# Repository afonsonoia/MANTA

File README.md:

# MANTA – Embedded AI & Vision-Guided Autonomous Flight Platform

**MANTA** is an experimental fixed-wing UAV research platform designed for investigating embedded computer vision, attitude stabilization, and autonomous navigation in GPS-denied environments.

Rather than relying on commercial black-box autopilots, MANTA is engineered from the ground up as an open, modular avionics architecture: combining low-level deterministic real-time control (ESP32) with high-level onboard perception and video recording (Raspberry Pi 3 A+ companion computer).

> **Origin of the Name**: *MANTA* is a regional term from Madeira Island, Portugal, designating the local population of the Common Buzzard (*Buteo buteo rothschildi*), a resident bird of prey known for soaring effortlessly across the island's steep oceanic mountains.

---

## In-Flight Validation & Onboard Camera Footage

MANTA has achieved fully stabilized flight under closed-loop fly-by-wire control with calibrated attitude PIDs, verified aerodynamic handling, and active onboard video recording.

The companion computer (**Raspberry Pi 3 A+**) flies onboard with a dedicated camera module, executing an autonomous power-loss-immune recording pipeline (`.mkv`) with sport shutter tuning to eliminate motor vibration artifacts and rolling shutter jello.

### Onboard Flight Video

<p align="center">
  
  <br>
  <em>▶️ <b>Watch the flight video</b> — Aerial footage captured directly by the onboard Raspberry Pi 3 A+ camera during flight tests. <b><a href="https://www.youtube.com/watch?v=h6kUTQn7zuM&t=90s" target="_blank">Click here or on the image above to play on YouTube starting at 1:30 min</a></b>.</em>
</p>

### Pre-Flight Preparation & Avionics Checkout

<p align="center">
  
  <br>
  <em>Pre-flight checkout at the flight field: LiPo battery installation, 6-axis IMU zeroing, radio link verification, and autonomous companion computer boot sequence before launch.</em>
</p>

During field operations, pre-flight checks verify the full avionics chain:
1. **Airframe & Propulsion**: 4S LiPo battery securement, Hobbywing Skywalker 40A V2 ESC throttle arming, and control horn linkage checks.
2. **IMU & Attitude Zeroing**: Static 6-axis MPU6050 accelerometer and gyroscope calibration with mounting offsets (+9.2° Pitch, +4.4° Roll).
3. **Control Surface Trims**: V-tail ruddervator and elevon zero-point verification across all 4 servos within calibrated hardware limits.
4. **LoRa Telemetry Handshake**: 20 Hz binary telemetry downlink reception and acoustic buzzer confirmation on the Ground Station ESP32.
5. **Companion Boot**: Autonomous transition of the Raspberry Pi 3 A+ into Field Mode with RF blocking and continuous video capture.

---

## Avionics & Embedded Hardware Architecture

MANTA uses a custom-manufactured dual-board shield architecture designed in KiCad, cleanly distributing high-current motor power and low-noise sensor signals while fitting into the airframe fuselage.

<p align="center">
  
  <br>
  <em>Complete assembled avionics stack: Custom dual-board PCB shield, ESP32 flight controller, LoRa 433 MHz RF link, Air530 GPS antenna, dual LM2596S switching buck converters, precision voltage divider, and Hobbywing Skywalker 40A V2-UBEC ESC.</em>
</p>

### Core Hardware Components

| Subsystem | Component | Role / Specification |
|---|---|---|
| **Flight Controller** | ESP32-WROOM-32 (240 MHz Dual-Core) | Real-time 100 Hz attitude estimation, RC receiver pulse decoding, PI-D control loops, V-tail servo mixing, and 20 Hz LoRa telemetry. |
| **Companion Computer** | Raspberry Pi 3 A+ (64-bit Quad-Core) | Camera management, high-bitrate in-flight video recording, visual place recognition (VPR), and future autonomous vision navigation. |
| **In-Flight Camera** | Sony IMX378-79 Sensor Module | High-resolution aerial video capture, 2x2 binned low-latency readout, and visual feature extraction. |
| **Inertial Measurement (IMU)** | MPU6050 (6-Axis Accel / Gyro) | High-rate attitude determination running Mahony AHRS quaternion fusion filter at 100 Hz. |
| **Barometric Altimeter** | BMP280 | Static pressure sensing, relative barometric altitude tracking, and vertical velocity estimation over I2C. |
| **RF Telemetry Link** | SX1278 LoRa Transceiver (433 MHz) | Long-range 20 Hz binary telemetry downlink (SF7, BW 250 kHz, CR 4/5, CRC16) streaming flight dynamics to the ground. |
| **Satellite Navigation** | Air530 Multi-GNSS Module | Global positioning reference, ground track velocity, and satellite constellation tracking over hardware UART. |
| **Electronic Speed Control (ESC)** | Hobbywing Skywalker 40A V2-UBEC | 3S–4S LiPo motor speed control with integrated 5V/5A switching BEC powering the avionics bus. |
| **Power Regulation** | Dual LM2596S DC-DC Regulators | Independent 5.1V / 3A power rails dedicated to the Raspberry Pi companion computer and servo bus, isolating control logic from servo voltage sag. |
| **Battery Monitoring** | Precision Calibrated Voltage Divider | Calibrated ADC sensing validated to within 0.062V of multimeter ground truth across 3S/4S voltage curves. |

### Custom Manufactured PCB Shields

<p align="center">

  <br>
  <em>KiCad Dual-Board Shield Layouts: Power Distribution Board & Data / Sensor Board</em>
</p>

- **Two-Board Architecture**: Separates noisy high-current traces (motor ESC, LiPo leads, buck regulators) on the Power Board from sensitive analog sensors (MPU6050, BMP280, LoRa SPI bus, RC receiver lines) on the Data Board.
- **Continuous Ground Pours**: Low-impedance ground returns and copper shielding prevent motor/ESC switching noise from coupling into the RF frontend or ADC measurements.

### Pinout & GPIO Mapping

```
RC Receiver Inputs:                  Servo & ESC Outputs:
  CH1 (Roll / Rollerons): Pin D39      Back Right (BR / V-Tail): Pin D13
  CH2 (Pitch / Elevator): Pin D34      Back Left  (BL / V-Tail): Pin D14
  CH3 (Throttle / ESC):   Pin D35      Front Right (FR / Flap):  Pin D27
  CH4 (Aux / Rudder):     Pin D32      Front Left  (FL / Flap):  Pin D26
  CH5 (Mode SWC + SWB):   Pin D33      Motor Throttle / ESC:     Pin D25

Buses & Peripherals:
  LoRa SX1278 (VSPI):     SCK=18, MISO=19, MOSI=23, CS=5, DIO0=4
  I2C Sensors (IMU+BMP):  SDA=21, SCL=22
  Air530 GNSS (UART2):    RX2=16, TX2=17
  Battery Voltage ADC:    Pin D36 (VP)
```

---

## Flight Control Architecture & Calibrated PIDs

MANTA utilizes a hybrid V-tail mixing scheme where Pitch is controlled by the rear ruddervators (BR/BL) and Roll is controlled by the front control surfaces (FR/FL), with elevator assist.

```mermaid
flowchart TD
    subgraph Inputs [Pilot & Sensor Inputs]
        RC[RC Receiver CH1-CH5]
        IMU[MPU6050 6-Axis IMU]
        BARO[BMP280 Barometer]
    end

    subgraph StateEst [Attitude Estimation]
        IMU --> Mahony[100 Hz Mahony AHRS Filter]
        Mahony --> Att[Pitch & Roll Euler Angles]
    end

    subgraph ControlCore [Flight Control Core]
        RC --> ModeSelect{Flight Mode Selector\nCH5 SWC + SWB}
        Att --> ModeSelect

        ModeSelect -->|Mode 1| M1[Manual Pitch + Roll Assist]
        ModeSelect -->|Mode 2| M2[FBW Pitch PI-D + FBW Roll PI-D]
        ModeSelect -->|Mode 3| M3[FBW Pitch PI-D + Adaptive Extremum Seeking Roll]

        SWB{Flaperons SWB} -->|Active| Flaps[20° Down Flaperon Governor]
    end

    subgraph Mixing [Actuator Mixer & Anti-Saturation]
        M1 & M2 & M3 --> Mixer[V-Tail & Wing Mixer]
        Flaps --> Mixer
        Mixer --> Headroom[Headroom Scaling & Anti-Saturation]
    end

    subgraph Outputs [Physical Actuators]
        Headroom --> Servos[BR / BL / FR / FL Servos + ESC]
    end
```

### Flight Modes (Transmitter CH5: SWC + SWB)

The pilot switches flight modes in real time via transmitter switches **SWC** (3-position mode switch) and **SWB** (2-position flaperon switch):

| SWC | SWB | CH5 PWM | Active Mode | Flaperons | Control Characteristics |
|:---:|:---:|:---:|:---:|:---:|:---|
| 1 | OFF | **1166 µs** | **Mode 1** | **OFF** | **Manual Pitch + Roll Assist**: Direct pilot pitch authority with active IMU bank angle attenuation and automatic wing leveling. |
| 2 | OFF | **1328 µs** | **Mode 2** | **OFF** | **FBW PI-D Auto-Level**: Closed-loop Pitch PI-D auto-leveling and Roll PI-D stabilization. |
| 3 | OFF | **1411 µs** | **Mode 3** | **OFF** | **FBW Adaptive**: Pitch PI-D leveling + Extremum Seeking adaptive roll PID tuning. |
| 1 | ON  | **1541 µs** | **Mode 1** | **ON**  | Manual Pitch + Roll Assist with **+20.0° DOWN Flaperons**. |
| 2 | ON  | **1825 µs** | **Mode 2** | **ON**  | FBW Pitch PI-D + Roll PI-D with **+20.0° DOWN Flaperons**. |
| 3 | ON  | **1942 µs** | **Mode 2** *(Auto)* | **ON**  | **Automatic Safety Demotion to Mode 2** + Flaperons (prevents adaptive gain corruption during approach). |

### Control Features & Safety Mechanisms

1. **Permanent Roll Assist (Mode 1)**:
   - Full ±20° pilot authority near wings level (0° roll).
   - Progressive linear bank angle attenuation up to 60°:
     $$\text{Max Roll Command} = 20^\circ \times \left(1 - \frac{|\text{Roll}|}{60^\circ}\right)$$
   - Active auto-recovery: If roll exceeds 60°, an automatic 5° opposite leveling bias is injected while retaining full pilot recovery command.
2. **Pitch PI-D Closed-Loop Control**:
   - Strictly negative feedback equation: $\text{pitchDiff} = -\text{constrain}(\text{pitchPidOut})$.
   - Anti-stall climb limit clamped to 25° ($K_p = 5.00$).
   - Anti-windup integrator ceiling limited to $\pm 100\,\mu\text{s}$ ($\pm 9.0^\circ$ of trim authority), guaranteeing 64% dynamic headroom for proportional and derivative action.
3. **Flaperons Approach Governor & Anti-Saturation**:
   - Deploys up to **+20.0° DOWN** ($\pm 222\,\mu\text{s}$) on front control surfaces (FR/FL) to dramatically increase lift coefficient ($C_L$) and drag ($C_D$) for slow, stable landings.
   - Smooth linear throttle governor between $1200\,\mu\text{s}$ (full deflection) and $1500\,\mu\text{s}$ (fully retracted).
   - **Headroom Scaling**: Pilot roll command maintains 100% priority. When roll commands approach mechanical limits, flaperon deflection is automatically scaled down (`flaperonHeadroom = 1.0 - |rollDiff| / anglePulseLimit`), preventing servo binding and maintaining roll control without clipping.

### Static Surface Calibration & Trims

All control surfaces operate strictly within the hardware safety span $[1000, 2000]\,\mu\text{s}$ centered around calibrated mechanical neutral points:

| Surface | Pin | Neutral PWM | Static Trim | Angular Span | Description |
|---|:---:|:---:|:---:|:---:|---|
| **BR (Back Right)** | D13 | **1478 µs** | $-2.0^\circ$ ($-22\,\mu\text{s}$) | $1200 - 1756\,\mu\text{s}$ | $+2.0^\circ$ UP nose-up compensation for level glide in manual mode. |
| **BL (Back Left)**  | D14 | **1633 µs** | $-12.0^\circ$ ($+133\,\mu\text{s}$) | $1355 - 1911\,\mu\text{s}$ | $+2.0^\circ$ UP inverted V-tail compensation. |
| **FR (Front Right)**| D27 | **1500 µs** | $0.0^\circ$ ($0\,\mu\text{s}$) | $1222 - 1778\,\mu\text{s}$ | True mechanical center. |
| **FL (Front Left)** | D26 | **1544 µs** | $+4.0^\circ$ ($+44\,\mu\text{s}$) | $1266 - 1822\,\mu\text{s}$ | Horn spline offset alignment defining flat wing zero. |

- **IMU Pitch Mounting Offset**: $+9.2^\circ$ (longitudinal leveling reference).
- **IMU Roll Mounting Offset**: $+4.4^\circ$ ($+1.9^\circ$ airframe bias $+ 2.5^\circ$ left-roll compensation for straight flight).

---

## Companion Computer & Video Pipeline (Raspberry Pi 3 A+)

The Raspberry Pi 3 A+ companion computer provides onboard vision processing and in-flight video capture:

```mermaid
flowchart LR
    Power[Power On Pi] --> BootService[manta-boot.service]
    BootService --> Check{Wi-Fi detected\n< 30 seconds?}

    Check -->|YES| DevMode[Bench / Dev Mode]
    DevMode --> GitPull[git pull]
    DevMode --> SSH[SSH & Wi-Fi Active]
    DevMode --> CamIdle[Camera Free for CV]

    Check -->|NO| FlightMode[Field / Flight Mode]
    FlightMode --> RFKill[rfkill: Block 2.4 GHz RF]
    FlightMode --> HDMIOff[Disable HDMI Circuitry]
    FlightMode --> AutoRec[Continuous .mkv Safe Recording]
```

### Autonomous Dual-Mode Boot Stack (`manta_boot.sh`)
- **Bench / Dev Mode (Wi-Fi Detected < 30s)**: Pi keeps Wi-Fi and SSH active, syncs codebase, and leaves the camera open for interactive computer vision development.
- **Field / Flight Mode (No Wi-Fi < 30s)**:
  - **RF Cutoff**: Disables Wi-Fi and Bluetooth (`rfkill block all`) to eliminate 2.4 GHz interference with the RC receiver and LoRa link while conserving battery power.
  - **HDMI Power-Down**: Shuts down the HDMI display subsystem (`vcgencmd display_power 0`), saving ~30 mA.
  - **Autonomous Safe Recording**: Launches `record_flight.sh` saving video directly to local storage.
- **Anti-Lockout Mechanism**: Multi-layer startup unblocking (`ExecStartPre=+`, NetworkManager re-activation, and interface scan) guarantees the Pi can reconnect to Wi-Fi whenever returning to the workshop.

### Power-Loss Immunity & Video Optimizations
- **Matroska (`.mkv`) Container**: Traditional MP4 files corrupt if power drops before the file header is finalized. MANTA records in Matroska with synchronous cluster flushing (`--flush`), ensuring video remains 100% playable right up to the exact moment the LiPo is disconnected upon landing.
- **Anti-Jello & Sport Shutter**: Uses 2x2 sensor pixel binning (halving sensor readout time), fast sport shutter exposure, manual focus locked to infinity, and temporal denoiser disabled to prevent motion blur and rolling shutter vibration skew.

---

## Ground Station & Telemetry Architecture

<p align="center">
  
  <br>
  <em>Dedicated Ground Station hardware: ESP32 receiver, 433 MHz LoRa module, and piezo acoustic warning buzzer streaming live telemetry over USB to the PC Mission Planner.</em>
</p>

### Simplex Downlink Protocol
- **Aircraft Transmitter (Simplex TX)**: Transmits 20 Hz binary telemetry packets (61 bytes nominal / up to 74 bytes with GNSS and failsafe data) protected by CRC16. The aircraft has no LoRa receiver listening overhead, ensuring uninterrupted flight control loop execution.
- **Ground Station Receiver (Simplex RX)**: Receives LoRa packets and streams them over USB Serial (`115200 baud`) to the PC Ground Station application while driving an onboard piezo buzzer.
- **Acoustic Warning System**: Emits audible alerts for link loss, critical battery states, and distinct 700 ms confirmation beeps upon flight mode transitions (SWC/SWB).

### Ground Station Software Suite

| Tool | Path | Description |
|---|---|---|
| **Mission Planner** | [`Code/GROUND-STATION/MANTA_MISSION_PLANNER.py`](file:///c:/Users/Afonso%20Noia/PycharmProjects/BlueSky/Code/GROUND-STATION/MANTA_MISSION_PLANNER.py) | Full-featured PC HUD displaying artificial horizon, compass, altitude, battery gauge, RSSI/SNR signal metrics, GPS map tracking, and flight mode state. |
| **Flight Replay Simulator** | [`Code/GROUND-STATION/replay_flight_mission_planner.py`](file:///c:/Users/Afonso%20Noia/PycharmProjects/BlueSky/Code/GROUND-STATION/replay_flight_mission_planner.py) | Replays recorded flight logs (`flight_logs/manta_flight_XXXX.csv`) through the Mission Planner HUD for post-flight analysis. |
| **FPV Explorer** | [`Code/Computer Vision/manta_explorer.py`](file:///c:/Users/Afonso%20Noia/PycharmProjects/BlueSky/Code/Computer Vision/manta_explorer.py) | Desktop GUI for previewing, browsing, and inspecting in-flight camera videos captured by the Raspberry Pi. |
| **Video Retrieval** | [`Code/Computer Vision/download_videos.py`](file:///c:/Users/Afonso%20Noia/PycharmProjects/BlueSky/Code/Computer Vision/download_videos.py) | Automated tool for pulling flight recordings from the Raspberry Pi over SCP/SFTP. |
| **PID SysID Tuner** | [`Code/GROUND-STATION/tune_pid_sysid.py`](file:///c:/Users/Afonso%20Noia/PycharmProjects/BlueSky/Code/GROUND-STATION/tune_pid_sysid.py) | System identification and PID tuning tool using recorded flight telemetry. |

---

## Repository Structure

```
├── .agents/                        # Aircraft configuration, pin mapping & control rules
├── Code/
│   ├── Battery_Monitor/            # Battery voltage calibration and ESC logger GUI
│   ├── Computer Vision/
│   │   ├── demos/                  # Visual Place Recognition (VPR) MobileNet + KNN experiments
│   │   ├── Simulator/              # Python flight dynamics simulator & PID visualization
│   │   ├── convert_videos.py       # H.264 / MKV video converter & re-muxer
│   │   ├── download_videos.py      # Automated flight video downloader from Raspberry Pi
│   │   └── manta_explorer.py       # Desktop FPV video explorer and review GUI
│   ├── GROUND-STATION/
│   │   ├── include/ & src/         # ESP32 Ground Station receiver firmware (PlatformIO)
│   │   ├── MANTA_MISSION_PLANNER.py # PC HUD Ground Station & telemetry dashboard
│   │   ├── replay_flight_mission_planner.py # Post-flight telemetry replay tool
│   │   ├── telemetry_codec.py      # Python binary telemetry packet encoder/decoder
│   │   ├── telemetry_csv_logger.py # Asynchronous high-rate flight log recorder
│   │   └── tune_pid_sysid.py       # Telemetry-based PID tuning and SysID analyzer
│   ├── MANTA_ESP32/
│   │   ├── include/ & src/         # Main flight controller C++ firmware (PlatformIO)
│   │   │   ├── control.cpp         # 100 Hz PI-D, Roll Assist, Flaperons governor & mixer
│   │   │   ├── mpu6050.cpp         # Mahony AHRS quaternion attitude estimation
│   │   │   ├── receiver.cpp        # 5-channel RC pulse decoder & deadband filtering
│   │   │   ├── network.cpp         # 20 Hz binary LoRa telemetry transmission
│   │   │   ├── bmp280.cpp          # I2C barometric altitude & pressure tracking
│   │   │   └── gps.cpp             # Hardware UART GNSS parsing & auto-pin detection
│   │   └── platformio.ini          # ESP32 build configuration & dependencies
│   └── MANTA_PI/
│       ├── manta_boot.sh           # Autonomous dual-mode boot manager (Bench vs Flight)
│       ├── manta-boot.service      # Systemd boot service for Raspberry Pi
│       ├── record_flight.sh        # Power-loss safe in-flight video recording
│       └── stream_flight.sh        # Low-latency live video streaming script
├── Electronics/
│   ├── DATA/                       # KiCad PCB layout & schematic (Data / Sensor Board)
│   └── POWER/                      # KiCad PCB layout & schematic (Power Distribution Board)
├── media/
│   └── general_images/             # Flight banner, in-flight video thumbnail, hardware photos & PCB layouts
├── tests/                          # 171 automated CI/CD unit & integration tests
└── run_tests.py                    # Master CI/CD test runner
```

---

## CI/CD Test Suite & Verification

The codebase includes an extensive automated test suite covering firmware compilation, control kinematics, telemetry codecs, fail-safes, and analytical sensor accuracy:

```bash
python run_tests.py
```

```
============================================================================
                  MANTA AVIONICS CI/CD TEST SUITE RUNNER            
============================================================================
  SUCCESS: All 171 MANTA CI/CD tests PASSED cleanly! (53.82s)
  Categories Verified:
    [PASS] Firmware & Python Compilation (PlatformIO ESP32 & Ground Station)
    [PASS] Fly-By-Wire Control, PI-D & Kinematics
    [PASS] Simplex Telemetry Codec & Protocols (Fuzzing, Bit-Corruption Rejection)
    [PASS] Flight Safety, Failsafes & SysID Alignment
    [PASS] Sensor Calibration & Ground Truth Verification (Voltage error < 0.062V)
============================================================================
```

---

## Project Roadmap

### Phase 1: Hardware Proof-of-Concepts (POC)
- [x] Establish ESP32 communications with peripheral sensors (BMP280, LoRa, Voltage sensor).
- [x] Implement RC receiver pulse width reading and telemetry logs.
- [x] Establish initial LoRa communication between aircraft and ground station.
- [x] Set up lightweight visual place recognition experiments using aerial imagery databases.
- [x] Perform isolated bench tests for each sensor to ensure accuracy and data reliability.

### Phase 2: Airframe Assembly & Avionics Integration
- [x] Assemble the main airframe skeleton and mount propulsion/control surfaces.
- [x] Complete custom KiCad PCB schematics and dual-board layout routing.
- [x] Manufacture physical dual-board PCB shield architecture (Power & Data boards).
- [x] Validate power distribution, dual BEC outputs, and sensor bus continuity.
- [x] Experimentally calibrate battery voltage conversion against multimeter ground truth (< 0.062V error).
- [x] Mount core avionics and electronics on the airframe.
- [x] Conduct EMI testing ensuring motor/ESC switching noise does not disrupt GPS or LoRa RF link.
- [x] Deploy robust LoRa telemetry (20 Hz binary codec, non-blocking Ground Station logging).
- [x] Execute maiden field flights in manual mode to validate airframe aerodynamics and ground station link.

### Phase 3: Flight Control & Fly-By-Wire Stabilization
- [x] Integrate 6-axis MPU6050 Mahony AHRS quaternion sensor fusion (100 Hz) into ESP32 firmware.
- [x] Implement attitude-aware roll envelope protection and progressive bank angle limiting on RC Channel 5.
- [x] Implement and calibrate closed-loop PI-D controllers for Pitch (rear V-tail) and Roll (front surfaces).
- [x] Implement 20° flaperons approach governor with dynamic headroom anti-saturation scaling.
- [x] Conduct field flight tests to calibrate PIDs for smooth, wind-resistant fly-by-wire leveling.
- [x] Mount and integrate Raspberry Pi 3 A+ companion computer and onboard camera module.
- [x] Deploy autonomous dual-mode boot stack and power-loss-immune flight video recording (`.mkv`).
- [x] Validate closed-loop flight stability and record in-flight aerial footage.

### Phase 4: Autonomous Waypoint Navigation & Path-Planning
- [ ] Implement interactive trajectory planner in PC Ground Station UI to select waypoints on a map.
- [ ] Transmit pre-planned path coordinates from Mission Planner to aircraft over wireless link.
- [ ] Develop onboard navigation controller fusing GPS, BMP280 barometric altitude, and IMU data.
- [ ] Validate autonomous waypoint-to-waypoint navigation, altitude hold, heading lock, and fail-safe Return-to-Home (RTH).
- [ ] Execute autonomous field flight missions to verify trajectory accuracy and fail-safe reliability.

### Phase 5: Onboard Vision & Visual Place Recognition (VPR)
- [x] Design custom mount and install Raspberry Pi 3 A+ companion computer and camera module on airframe.
- [x] Execute onboard high-rate video logging and autonomous flight capture.
- [ ] Set up ESP32-to-Raspberry Pi high-speed serial communication protocol (UART / telemetry bridge).
- [ ] Deploy lightweight Visual Place Recognition (VPR) for image-based GPS-denied position estimation.
- [ ] Develop computer vision pipelines for visual horizon detection and landmark/mountain recognition.
- [ ] Test real-time visual perception and localization during autonomous flight.
- [ ] Perform comprehensive flight campaigns evaluating vision-based localization precision under real operational conditions.

---

## Authors & Acknowledgments

- **Afonso Nóia** — Aircraft design, custom PCB hardware, firmware development, fly-by-wire control algorithms, companion computer software, and flight testing.
- Platform development and field testing conducted on Madeira Island, Portugal.

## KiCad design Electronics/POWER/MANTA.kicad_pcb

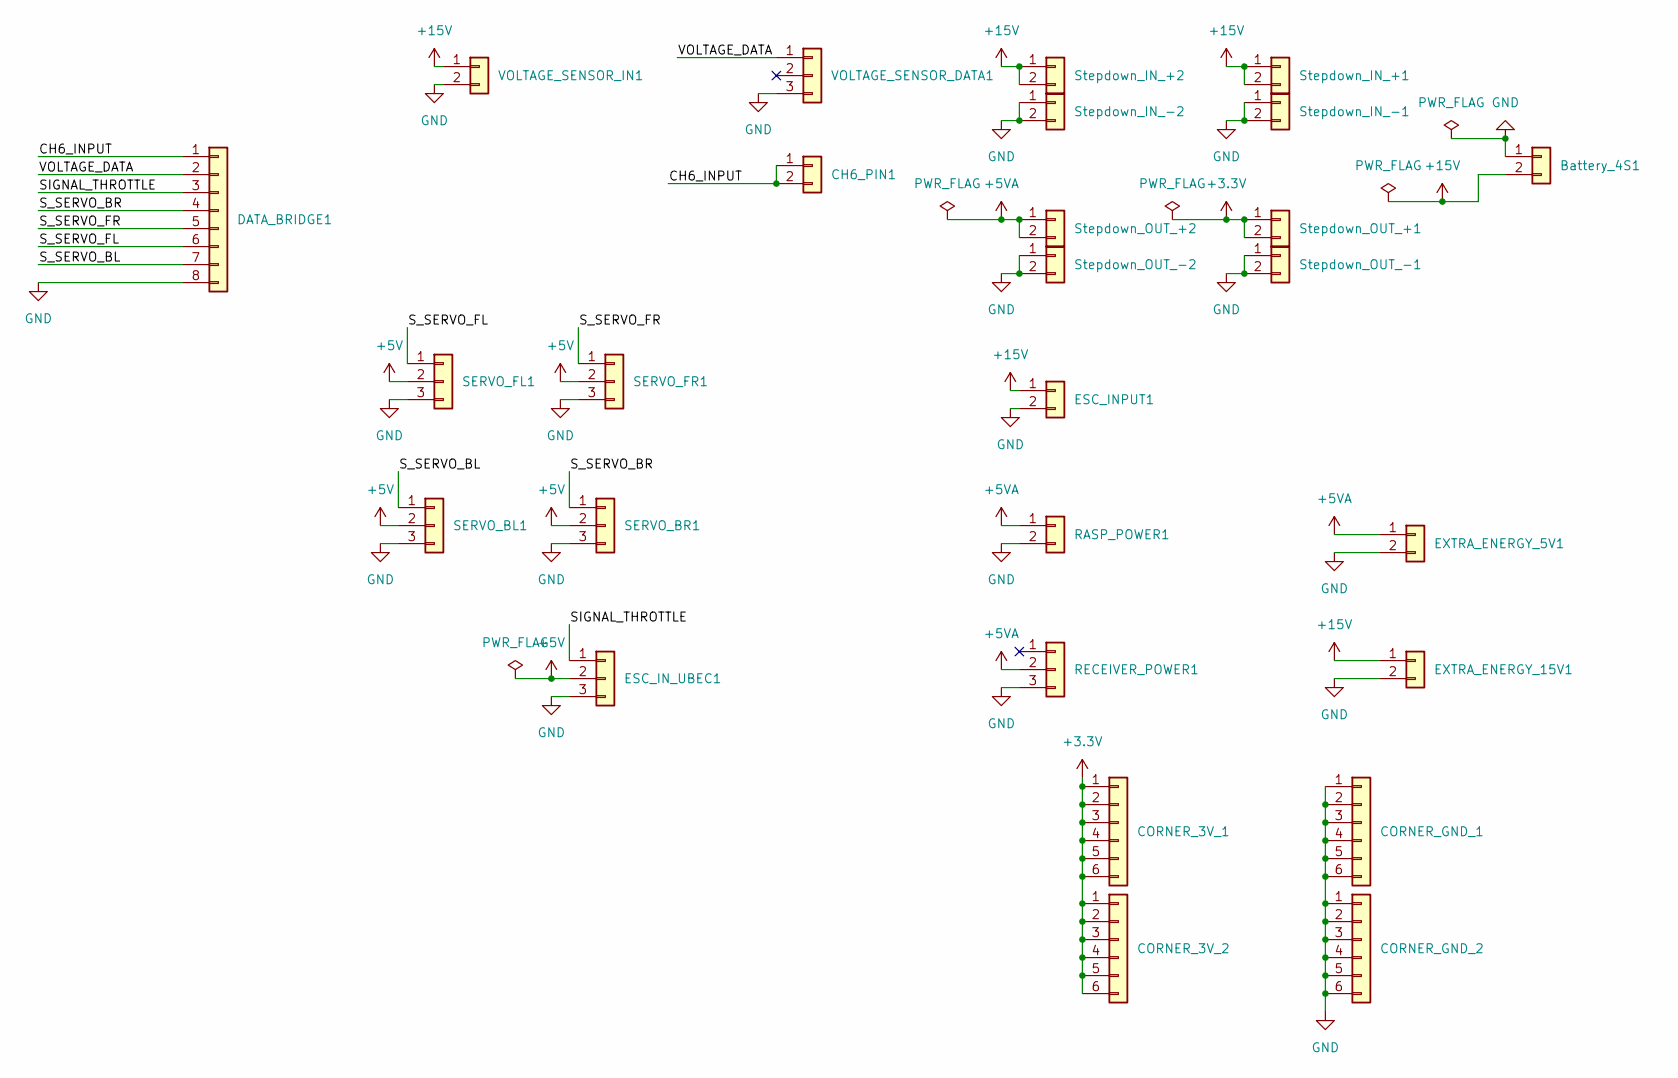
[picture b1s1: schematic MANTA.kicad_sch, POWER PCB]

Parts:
Battery_4S1: Conn_01x02; AMASS_XT60PW-M_1x02_P7.20mm_Horizontal
CH6_PIN1: Conn_01x02; PinHeader_1x02_P2.54mm_Vertical
CORNER_3V_1, CORNER_3V_2: Conn_01x06; PinHeader_1x06_P2.54mm_Vertical
CORNER_GND_1, CORNER_GND_2: Conn_01x06; PinHeader_1x06_P2.54mm_Vertical
DATA_BRIDGE1: Conn_01x08; PinHeader_1x08_P2.54mm_Vertical
ESC_INPUT1: SolderWire-2.5sqmm_1x02_P8.8mm_D2.4mm_OD4.4mm
ESC_IN_UBEC1: Conn_01x03; PinHeader_1x03_P2.54mm_Vertical
EXTRA_ENERGY_5V1, EXTRA_ENERGY_15V1: Conn_01x02; PinHeader_1x02_P2.54mm_Vertical
RASP_POWER1: Conn_01x02; PinHeader_1x02_P2.54mm_Vertical
RECEIVER_POWER1: Conn_01x03; PinHeader_1x03_P2.54mm_Vertical
SERVO_BL1: Conn_01x03; PinHeader_1x03_P2.54mm_Vertical
SERVO_BR1: Conn_01x03; PinHeader_1x03_P2.54mm_Vertical
SERVO_FL1: Conn_01x03; PinHeader_1x03_P2.54mm_Vertical
SERVO_FR1: Conn_01x03; PinHeader_1x03_P2.54mm_Vertical
Stepdown_IN_+1, Stepdown_IN_+2: Conn_01x02; PinHeader_1x02_P2.54mm_Vertical
Stepdown_IN_-1, Stepdown_IN_-2: Conn_01x02; PinHeader_1x02_P2.54mm_Vertical
Stepdown_OUT_+1, Stepdown_OUT_+2: Conn_01x02; PinHeader_1x02_P2.54mm_Vertical
Stepdown_OUT_-1, Stepdown_OUT_-2: Conn_01x02; PinHeader_1x02_P2.54mm_Vertical
VOLTAGE_SENSOR_DATA1: Conn_01x03; PinHeader_1x03_P2.54mm_Vertical
VOLTAGE_SENSOR_IN1: PinHeader_1x02_P2.54mm_Vertical

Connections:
+3.3V: CORNER_3V_1.1, CORNER_3V_1.2, CORNER_3V_1.3, CORNER_3V_1.4, CORNER_3V_1.5, CORNER_3V_1.6, CORNER_3V_2.1, CORNER_3V_2.2, CORNER_3V_2.3, CORNER_3V_2.4, CORNER_3V_2.5, CORNER_3V_2.6, Stepdown_OUT_+1.1, Stepdown_OUT_+1.2
+5V: ESC_IN_UBEC1.2, SERVO_BL1.2, SERVO_BR1.2, SERVO_FL1.2, SERVO_FR1.2
+5VA: EXTRA_ENERGY_5V1.1, RASP_POWER1.1, RECEIVER_POWER1.2, Stepdown_OUT_+2.1, Stepdown_OUT_+2.2
+15V: Battery_4S1.2, ESC_INPUT1.1, EXTRA_ENERGY_15V1.1, Stepdown_IN_+1.1, Stepdown_IN_+1.2, Stepdown_IN_+2.1, Stepdown_IN_+2.2, VOLTAGE_SENSOR_IN1.1
/CH6_INPUT: CH6_PIN1.1, CH6_PIN1.2, DATA_BRIDGE1.1
/SIGNAL_THROTTLE: DATA_BRIDGE1.3, ESC_IN_UBEC1.1
/S_SERVO_BL: DATA_BRIDGE1.7, SERVO_BL1.1
/S_SERVO_BR: DATA_BRIDGE1.4, SERVO_BR1.1
/S_SERVO_FL: DATA_BRIDGE1.6, SERVO_FL1.1
/S_SERVO_FR: DATA_BRIDGE1.5, SERVO_FR1.1
/VOLTAGE_DATA: DATA_BRIDGE1.2, VOLTAGE_SENSOR_DATA1.1
GND: Battery_4S1.1, CORNER_GND_1.1, CORNER_GND_1.2, CORNER_GND_1.3, CORNER_GND_1.4, CORNER_GND_1.5, CORNER_GND_1.6, CORNER_GND_2.1, CORNER_GND_2.2, CORNER_GND_2.3, CORNER_GND_2.4, CORNER_GND_2.5, CORNER_GND_2.6, DATA_BRIDGE1.8, ESC_INPUT1.2, ESC_IN_UBEC1.3, EXTRA_ENERGY_5V1.2, EXTRA_ENERGY_15V1.2, RASP_POWER1.2, RECEIVER_POWER1.3, SERVO_BL1.3, SERVO_BR1.3, SERVO_FL1.3, SERVO_FR1.3, Stepdown_IN_-1.1, Stepdown_IN_-1.2, Stepdown_IN_-2.1, Stepdown_IN_-2.2, Stepdown_OUT_-1.1, Stepdown_OUT_-1.2, Stepdown_OUT_-2.1, Stepdown_OUT_-2.2, VOLTAGE_SENSOR_DATA1.3, VOLTAGE_SENSOR_IN1.2

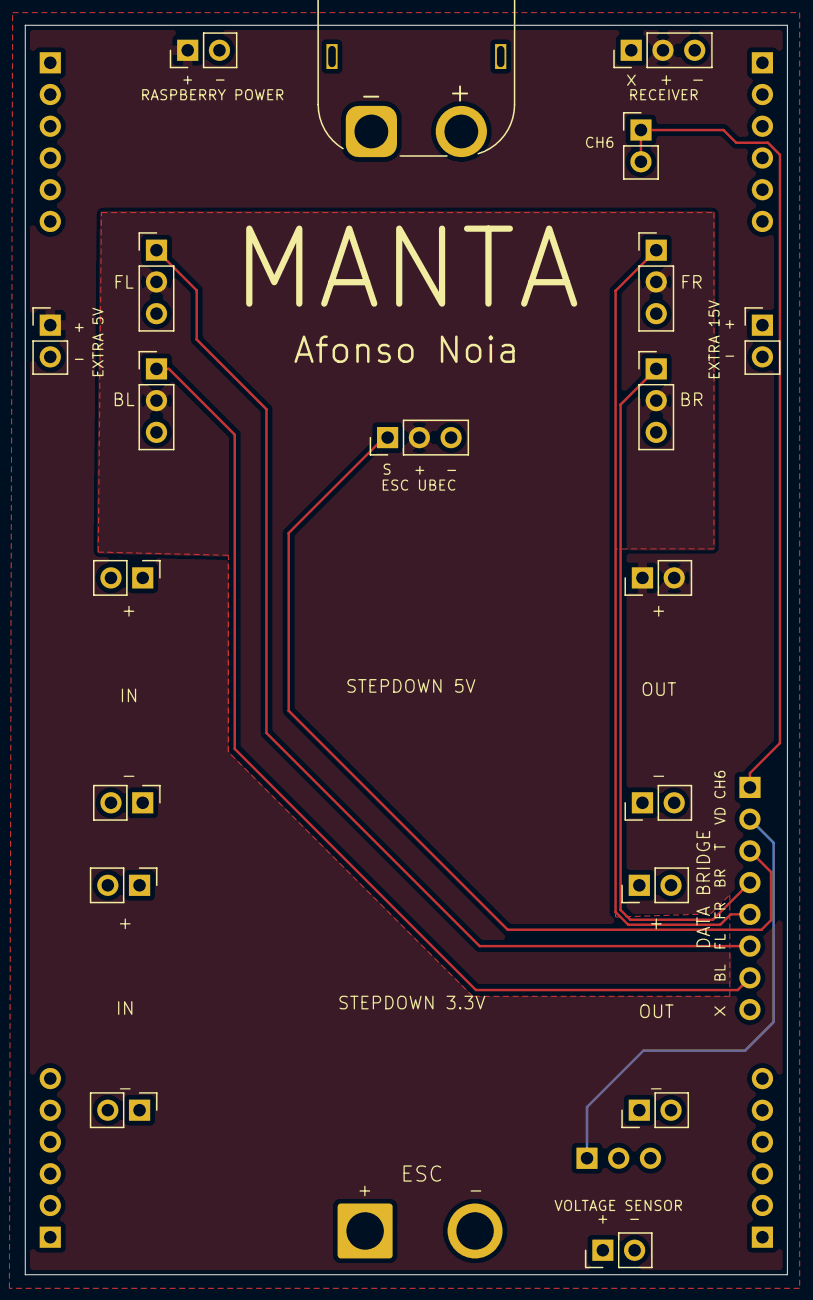
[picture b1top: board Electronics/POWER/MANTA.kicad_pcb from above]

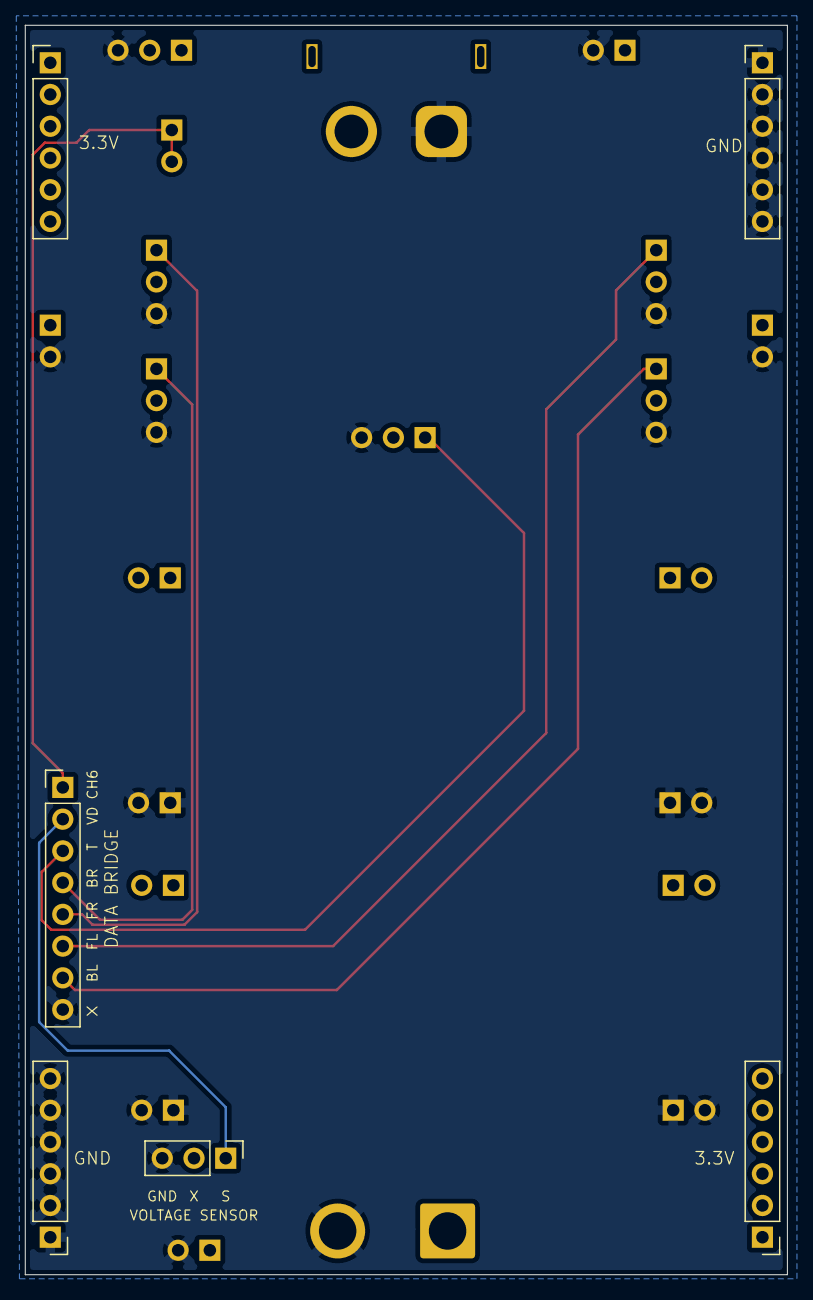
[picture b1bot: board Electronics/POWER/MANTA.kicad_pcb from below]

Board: 4 copper layers, 61.0 x 100.0 mm, 27 parts (6 on the bottom side), 12 nets.

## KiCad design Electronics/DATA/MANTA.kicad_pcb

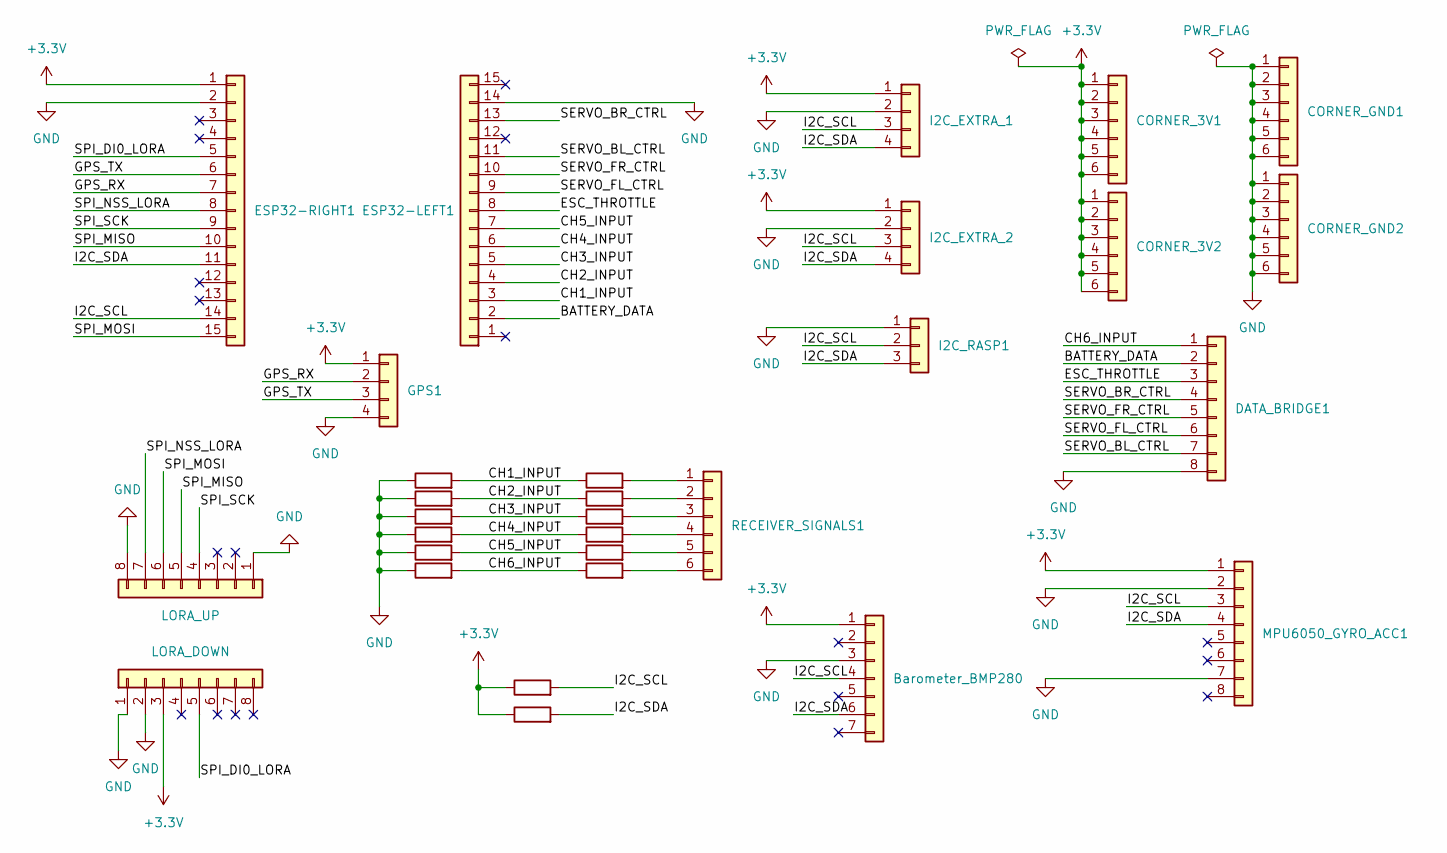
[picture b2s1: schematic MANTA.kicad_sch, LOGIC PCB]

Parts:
Barometer_BMP280: Conn_01x07; PinHeader_1x07_P2.54mm_Vertical
CORNER_3V1, CORNER_3V2: Conn_01x06; PinHeader_1x06_P2.54mm_Vertical
CORNER_GND1, CORNER_GND2: Conn_01x06; PinHeader_1x06_P2.54mm_Vertical
DATA_BRIDGE1: Conn_01x08; PinHeader_1x08_P2.54mm_Vertical
ESP32-LEFT1, ESP32-RIGHT1: Conn_01x15; PinHeader_1x15_P2.54mm_Vertical
GPS1: Conn_01x04; PinHeader_1x04_P2.54mm_Vertical
I2C_EXTRA_1, I2C_EXTRA_2: Conn_01x04; PinHeader_1x04_P2.54mm_Vertical
I2C_RASP1: Conn_01x03; PinHeader_1x03_P2.54mm_Vertical
J1: LORA_UP; PinHeader_1x08_P2.54mm_Vertical
J2: LORA_DOWN; PinHeader_1x08_P2.54mm_Vertical
MPU6050_GYRO_ACC1: Conn_01x08; PinHeader_1x08_P2.54mm_Vertical
R1, R2, R3, R4, R5, R6: 1k; R_Axial_DIN0207_L6.3mm_D2.5mm_P10.16mm_Horizontal
R7, R8, R9, R10, R11, R12: 2k; R_Axial_DIN0207_L6.3mm_D2.5mm_P10.16mm_Horizontal
R13, R14: 10k; R_Axial_DIN0207_L6.3mm_D2.5mm_P10.16mm_Horizontal
RECEIVER_SIGNALS1: Conn_01x06; PinHeader_1x06_P2.54mm_Vertical

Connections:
+3.3V: Barometer_BMP280.1, CORNER_3V1.1, CORNER_3V1.2, CORNER_3V1.3, CORNER_3V1.4, CORNER_3V1.5, CORNER_3V1.6, CORNER_3V2.1, CORNER_3V2.2, CORNER_3V2.3, CORNER_3V2.4, CORNER_3V2.5, CORNER_3V2.6, ESP32-RIGHT1.1, GPS1.1, I2C_EXTRA_1.1, I2C_EXTRA_2.1, J2.3, MPU6050_GYRO_ACC1.1, R13.1, R14.1
/BATTERY_DATA: DATA_BRIDGE1.2, ESP32-LEFT1.2
/CH1_INPUT: ESP32-LEFT1.3, R1.1, R7.2
/CH2_INPUT: ESP32-LEFT1.4, R2.1, R8.2
/CH3_INPUT: ESP32-LEFT1.5, R3.1, R9.2
/CH4_INPUT: ESP32-LEFT1.6, R4.1, R10.2
/CH5_INPUT: ESP32-LEFT1.7, R5.1, R11.2
/CH6_INPUT: DATA_BRIDGE1.1, R6.1, R12.2
/ESC_THROTTLE: DATA_BRIDGE1.3, ESP32-LEFT1.8
/GPS_RX: ESP32-RIGHT1.7, GPS1.2
/GPS_TX: ESP32-RIGHT1.6, GPS1.3
/I2C_SCL: Barometer_BMP280.4, ESP32-RIGHT1.14, I2C_EXTRA_1.3, I2C_EXTRA_2.3, I2C_RASP1.2, MPU6050_GYRO_ACC1.3, R13.2
/I2C_SDA: Barometer_BMP280.6, ESP32-RIGHT1.11, I2C_EXTRA_1.4, I2C_EXTRA_2.4, I2C_RASP1.3, MPU6050_GYRO_ACC1.4, R14.2
/SERVO_BL_CTRL: DATA_BRIDGE1.7, ESP32-LEFT1.11
/SERVO_BR_CTRL: DATA_BRIDGE1.4, ESP32-LEFT1.13
/SERVO_FL_CTRL: DATA_BRIDGE1.6, ESP32-LEFT1.9
/SERVO_FR_CTRL: DATA_BRIDGE1.5, ESP32-LEFT1.10
/SPI_DI0_LORA: ESP32-RIGHT1.5, J2.5
/SPI_MISO: ESP32-RIGHT1.10, J1.5
/SPI_MOSI: ESP32-RIGHT1.15, J1.6
/SPI_NSS_LORA: ESP32-RIGHT1.8, J1.7
/SPI_SCK: ESP32-RIGHT1.9, J1.4
GND: Barometer_BMP280.3, CORNER_GND1.1, CORNER_GND1.2, CORNER_GND1.3, CORNER_GND1.4, CORNER_GND1.5, CORNER_GND1.6, CORNER_GND2.1, CORNER_GND2.2, CORNER_GND2.3, CORNER_GND2.4, CORNER_GND2.5, CORNER_GND2.6, DATA_BRIDGE1.8, ESP32-LEFT1.14, ESP32-RIGHT1.2, GPS1.4, I2C_EXTRA_1.2, I2C_EXTRA_2.2, I2C_RASP1.1, J1.1, J1.8, J2.1, J2.2, MPU6050_GYRO_ACC1.2, MPU6050_GYRO_ACC1.7, R7.1, R8.1, R9.1, R10.1, R11.1, R12.1
unnamed: R1.2, RECEIVER_SIGNALS1.1
unnamed: R2.2, RECEIVER_SIGNALS1.2
unnamed: R3.2, RECEIVER_SIGNALS1.3
unnamed: R4.2, RECEIVER_SIGNALS1.4
unnamed: R5.2, RECEIVER_SIGNALS1.5
unnamed: R6.2, RECEIVER_SIGNALS1.6

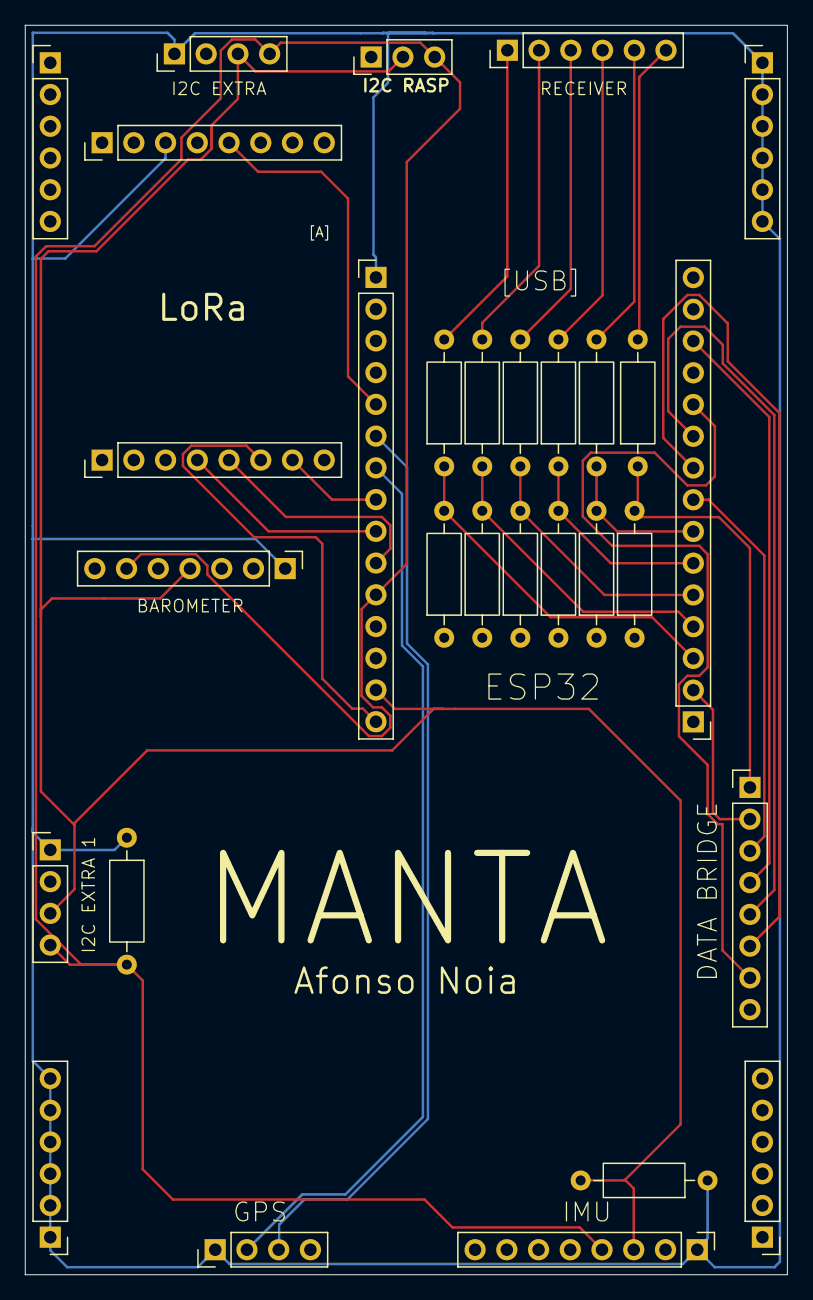
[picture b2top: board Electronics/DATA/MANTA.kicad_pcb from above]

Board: 2 copper layers, 61.0 x 100.0 mm, 30 parts (0 on the bottom side), 29 nets.

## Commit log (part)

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2026-01-02 Simple TCP communication example working
2026-01-03 Example 2: batometer data by TCP
2026-01-03 barometer + LoRa
2026-02-10 getting ready for flight test 2 (10/02/2026)
2026-03-09 general uptades
2026-06-25 refactor: restructure repository folders and update project roadmap
2026-06-30 Update electronics for hardware compatibility
    - Updated the schematic and KiCad project to align with the physical hardware purchased.
    - Replaced generic connectors with specific 2.54mm pitch vertical pin headers (1x07 and 1x02) for the ESP32 and power distribution modules.
    - Refactored power routing and replaced symbols (adjusting GND, +15V, and +5V).
    - Updated designators (e.g., ESP32-LEFT1, ESP32-RIGHT1, EXTRA_ENERGY_15V1) to correctly match the interfaces of the new physical components.
2026-06-30 Update electronics schematic
